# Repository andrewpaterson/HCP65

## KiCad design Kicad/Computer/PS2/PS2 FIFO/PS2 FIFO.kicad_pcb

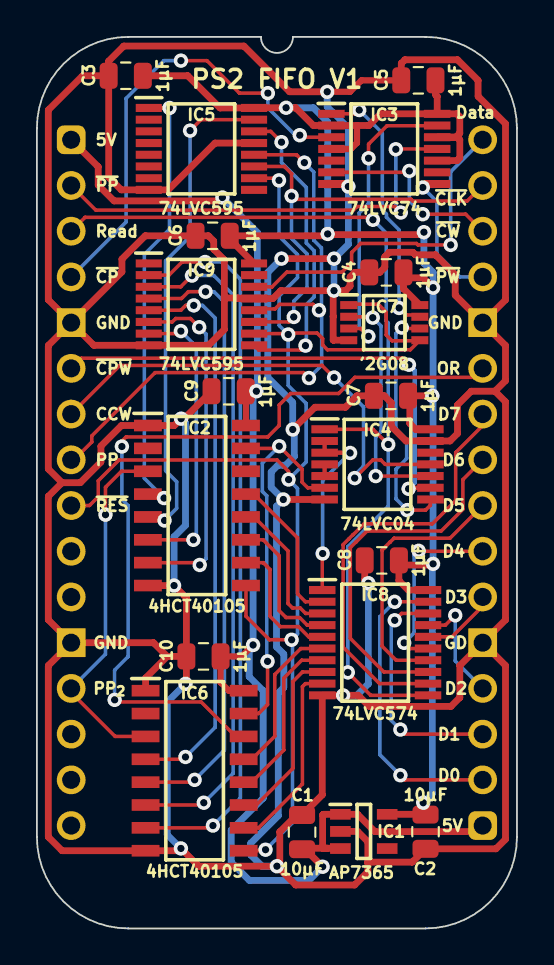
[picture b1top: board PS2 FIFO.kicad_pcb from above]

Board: 2 copper layers, 26.7 x 49.5 mm, 20 parts (0 on the bottom side), 48 nets.

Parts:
C1, C2: 10μF; C_0805
C3, C4, C5, C6, C7, C8, C9, C10: 1μF; C_0805
IC1: AP7365-33WG-7; SOT95P285X130-5N
IC2, IC6: CD74HCT40105M; SOIC127P600X175-16N
IC3: 74LVC74APW,118; SOP65P640X110-14N
IC4: 74LVC04APW,118; SOP65P640X110-14N
IC5, IC9: 74LVC595APW; SOP65P640X110-16N
IC7: 74LVC2G08DP-Q100H; SOP65P400X110-8N
IC8: 74LVC574APW,118; SOP65P640X110-20N
J1: Board 2x16 W22.86mm; DIP-32_Board_W22.86mm

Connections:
5V: C1.1, C9.1, C10.1, IC1.1 (6VIn), IC1.3 (EN), IC2.16 (5V), IC6.16 (5V), J1.1, J1.17
/3.3V: C2.1, C3.1, C4.1, C5.1, C6.1, C7.1, C8.1, IC1.5 (3.3VOut), IC3.2 (1D), IC3.4 (~1SD), IC3.10 (~2SD), IC3.12 (2D), IC3.14 (3V), IC4.14 (3V), IC5.16 (3V), IC7.8 (3V), IC8.20 (3V), IC9.16 (3V)
/Q0: IC2.4 (D0), IC5.1 (Q1)
/Q1: IC2.5 (D1), IC5.15 (Q0)
/Q2: IC2.6 (D2), IC9.7 (Q7)
/Q3: IC2.7 (D3), IC9.6 (Q6)
/Q4: IC6.4 (D0), IC9.5 (Q5)
/Q5: IC6.5 (D1), IC9.4 (Q4)
/Q6: IC6.6 (D2), IC9.3 (Q3)
/Q7: IC6.7 (D3), IC9.2 (Q2)
/Read_{2}: IC4.4 (2Y), IC4.5 (3A)
/S0: IC2.13 (Q0), IC8.2 (D0)
/S1: IC2.12 (Q1), IC8.3 (D1)
/S2: IC2.11 (Q2), IC8.4 (D2)
/S3: IC2.10 (Q3), IC8.5 (D3)
/S4: IC6.13 (Q0), IC8.6 (D4)
/S5: IC6.12 (Q1), IC8.7 (D5)
/S6: IC6.11 (Q2), IC8.8 (D6)
/S7: IC6.10 (Q3), IC8.9 (D7)
/~Clear Code Waiting: IC4.10 (5Y), IC7.2 (1B)
/~Clear Packet Waiting: IC4.8 (4Y), IC7.6 (2B)
/~Read: IC4.2 (1Y), IC4.3 (2A), IC8.1 (~OE)
/~Read_{3}: IC2.15 (~SO), IC4.6 (3Y), IC6.15 (~SO)
Clear Code Waiting: IC4.11 (5A), J1.7
Clear Packet Waiting: IC4.9 (4A), J1.6
D0: IC8.19 (Q0), J1.18
D1: IC8.18 (Q1), J1.19
D2: IC8.17 (Q2), J1.20
D3: IC8.16 (Q3), J1.22
D4: IC8.15 (Q4), J1.23
D5: IC8.14 (Q5), J1.24
D6: IC8.13 (Q6), J1.25
D7: IC8.12 (Q7), J1.26
Data: IC9.14 (DS), J1.32
GND: C1.2, C2.2, C3.2, C4.2, C5.2, C6.2, C7.2, C8.2, C9.2, C10.2, IC1.2 (GND), IC2.1 (~EN(TSC)), IC2.8 (GND), IC3.7 (GND), IC4.7 (GND), IC4.13 (6A), IC5.8 (GND), IC5.13 (~OE), IC6.1 (~EN(TSC)), IC6.8 (GND), IC7.4 (GND), IC8.10 (GND), IC9.8 (GND), IC9.13 (~OE), J1.5, J1.12, J1.21, J1.28
unnamed: IC3.1 (~1RD), IC7.7 (1Y)
unnamed: IC3.13 (~2RD), IC7.3 (2Y)
unnamed: IC5.14 (DS), IC9.9 (Q7S)
Output Ready: IC6.14 (DOR), J1.27
Packet Pulse: IC5.12 (STCP), IC9.12 (STCP), J1.8
Packet Pulse_{2}: IC2.3 (SI), IC6.3 (SI), J1.13
Read: IC4.1 (1A), IC8.11 (CP), J1.3
~Clock: IC5.11 (SHCP), IC9.11 (SHCP), J1.31
~Code Pulse: IC3.3 (1CP), J1.4
~Code Waiting: IC3.6 (~1Q), J1.30
~Packet Pulse: IC3.11 (2CP), J1.2
~Packet Waiting: IC3.8 (~2Q), J1.29
~Reset: IC2.9 (MR), IC5.10 (~MR), IC6.9 (MR), IC7.1 (1A), IC7.5 (2A), IC9.10 (~MR), J1.9

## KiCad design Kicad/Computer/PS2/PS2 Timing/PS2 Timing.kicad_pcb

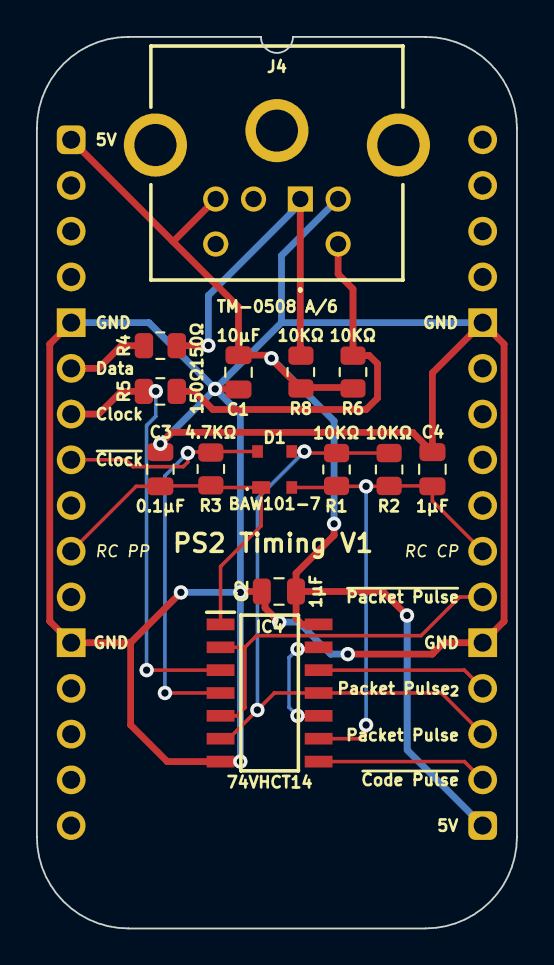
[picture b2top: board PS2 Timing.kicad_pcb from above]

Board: 2 copper layers, 26.7 x 49.5 mm, 15 parts (0 on the bottom side), 14 nets.

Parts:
C1: 10μF; C_0805
C2, C4: 1μF; C_0805
C3: 0.1μF; C_0805
D1: BAW101-7; BAW1017
IC4: 74VHCT14AM; SOIC127P600X175-14N
J2: Board 2x16 W22.86mm; DIP-32_Board_W22.86mm
J4: TM-0508 A/6; TM0508A6
R1, R2, R6, R8: 10KΩ; R_0805
R3: 4.7KΩ; R_0805
R4, R5: 150Ω; R_0805

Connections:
5V: C1.1, C2.1, IC4.14 (5V), J2.1, J2.17, J4.4, R6.2, R8.2
/Clock_{IN}: J4.5, R5.1, R6.1
/Data_{IN}: J4.1, R4.1, R8.1
/~Packet Pulse_{2}: IC4.10 (5Y), IC4.13 (6A)
Clock: IC4.3 (2A), J2.7, R5.2
Data: J2.6, R4.2
GND: C1.2, C2.2, C3.2, C4.2, IC4.7 (GND), J2.5, J2.12, J2.21, J2.28, J4.3
Packet Pulse: D1.3 (A2), IC4.6 (3Y), IC4.11 (5A), J2.19, R1.1, R2.1
Packet Pulse_{2}: IC4.12 (6Y), J2.20
RC Code Pulse: C4.1, D1.2 (K2), IC4.9 (4A), J2.23, R1.2, R2.2
RC Packet Pulse: C3.1, D1.1 (K1), IC4.1 (1A), J2.10, R3.2
~Clock: D1.4 (A1), IC4.4 (2Y), J2.8, R3.1
~Code Pulse: IC4.8 (4Y), J2.18
~Packet Pulse: IC4.2 (1Y), IC4.5 (3A), J2.22

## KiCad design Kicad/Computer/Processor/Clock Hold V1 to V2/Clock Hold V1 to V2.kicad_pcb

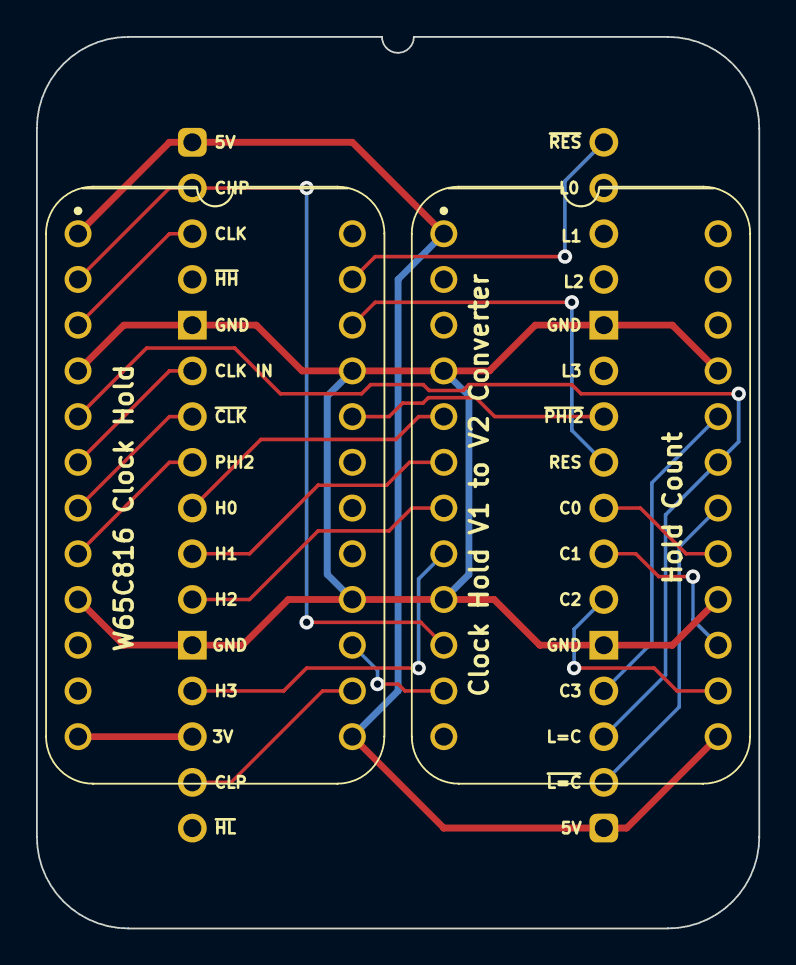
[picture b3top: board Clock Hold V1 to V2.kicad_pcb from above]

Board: 2 copper layers, 40.1 x 49.5 mm, 3 parts (0 on the bottom side), 23 nets.

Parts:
B22: W65C816 Clock Hold; HCP65_W65C816_Clock_Hold
B23: Hold Count; HCP65_Hold_Count
J1: Board 2x16 W22.86mm; DIP-32_Board_W22.86mm_Nak

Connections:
3.3V: B22.12 (~Hold_Low), J1.14
5V: B22.1 (5V), B22.13 (5V), B23.1 (5V), B23.13 (5V), J1.1, J1.17
/~CHP: B22.15 (~CLK_High_Pulse), B23.11 (~CLK_High_Pulse)
C0: B23.17 (Count0), J1.24
C1: B23.15 (Count1), J1.23
C2: B23.14 (Count2), J1.22
C3: B23.20 (Count3), J1.20
CHP: B22.2 (CLK_High_Pulse), B23.10 (CLK_High_Pulse), J1.2
CLK: B22.3 (CLK), J1.3
CLK IN: B22.6 (CLK_IN), J1.6
CLP: B22.14 (CLK_Low_Pulse), J1.15
GND: B22.4 (GND), B22.9 (GND), B22.16 (GND), B22.21 (GND), B23.4 (GND), B23.9 (GND), B23.16 (GND), B23.21 (GND), J1.5, J1.12, J1.21, J1.28
H0: B23.5 (Hold0), J1.9
H1: B23.6 (Hold1), J1.10
H2: B23.7 (Hold2), J1.11
H3: B23.8 (Hold3), J1.13
L=C: B22.5 (~Hold_High), B23.19 (L=C), J1.19
PHI2: B22.8 (PHI2), J1.8
Reset: B22.22 (Reset), J1.25
~CLK: B22.7 (~CLK), J1.7
~L=C: B23.18 (~L=C), J1.18
~PHI2: B22.20 (~PHI2), J1.26
~Reset: B22.23 (~Reset), J1.32

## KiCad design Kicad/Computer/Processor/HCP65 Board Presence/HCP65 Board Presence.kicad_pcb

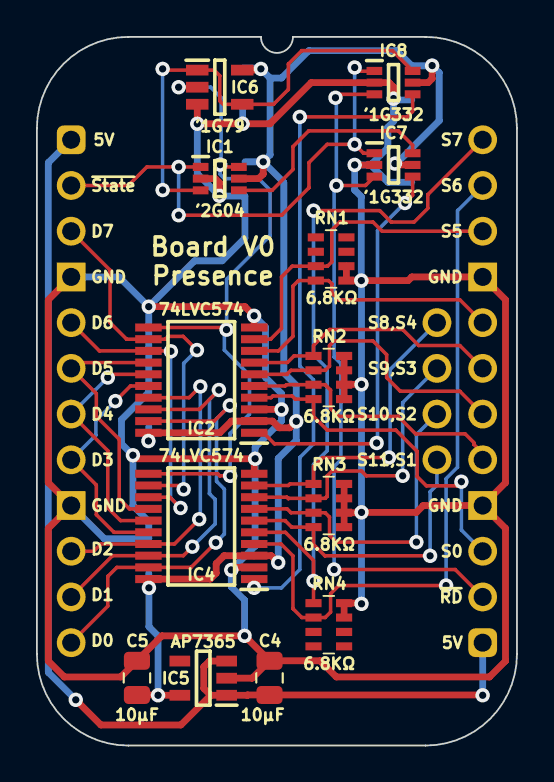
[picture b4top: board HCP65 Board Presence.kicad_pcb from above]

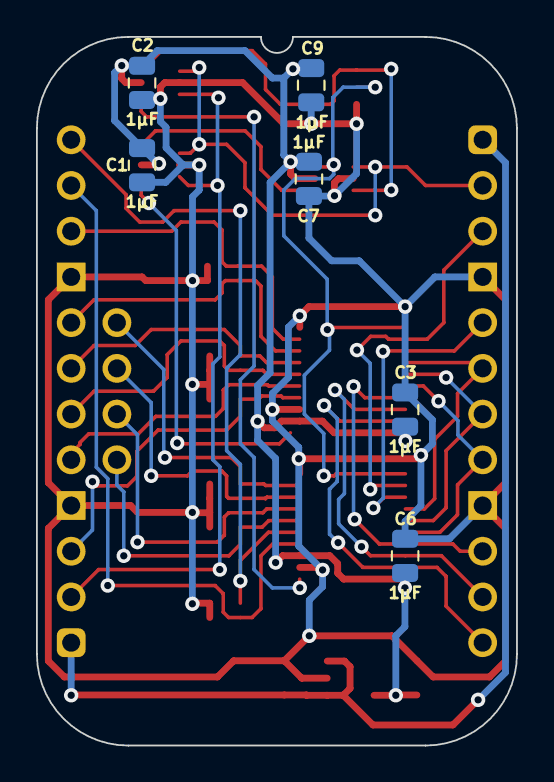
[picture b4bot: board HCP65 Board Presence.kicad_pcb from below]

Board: 2 copper layers, 26.7 x 39.4 mm, 21 parts (7 on the bottom side), 30 nets.

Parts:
C1, C2, C3, C6, C7, C9: 1μF; C_0805
C4, C5: 10µF; C_0805
IC1: 74LVC2G04GW-Q100H; SOP65P210X110-6N
IC2, IC4: 74LVC574APW,118; SOP65P640X110-20N
IC5: AP7365-33WG-7; SOT95P285X130-5N
IC6: 74LVC1G79GV,125; SOT95P275X110-5N
IC7, IC8: 74LVC1G332GW-Q100H; SOP65P210X110-6N
J1: Board 2x12 W22.86mm; DIP-24_Board_W22.86mm
J3: Conn_01x04_Pin; PinHeader_1x04_P2.54mm_Vertical
RN1, RN2, RN3, RN4: CAY16-682J4LF; CAY16-J4

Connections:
5V: C4.1, IC5.1 (6VIn), IC5.3 (EN), J1.1, J1.13
/3.3V: C1.1, C2.1, C3.1, C5.1, C6.1, C7.1, C9.1, IC1.5 (3V), IC2.2 (D0), IC2.20 (3V), IC4.3 (D1), IC4.20 (3V), IC5.5 (3.3VOut), IC6.5 (3V), IC7.5 (3V), IC8.5 (3V)
/Q: IC1.3 (2A), IC6.1 (D), IC6.4 (Q), IC8.6 (C)
/State: IC1.6 (1Y), IC2.11 (CP), IC4.11 (CP), IC6.2 (CP)
/~Q: IC1.4 (2Y), IC7.6 (C)
/~Read State0: IC2.1 (~OE), IC7.4 (Y)
/~Read State1: IC4.1 (~OE), IC8.4 (Y)
D0: IC2.19 (Q0), IC4.19 (Q0), J1.12
D1: IC2.18 (Q1), IC4.18 (Q1), J1.11
D2: IC2.17 (Q2), IC4.17 (Q2), J1.10
D3: IC2.16 (Q3), IC4.16 (Q3), J1.8
D4: IC2.15 (Q4), IC4.15 (Q4), J1.7
D5: IC2.14 (Q5), IC4.14 (Q5), J1.6
D6: IC2.13 (Q6), IC4.13 (Q6), J1.5
D7: IC2.12 (Q7), IC4.12 (Q7), J1.3
GND: C1.2, C2.2, C3.2, C4.2, C5.2, C6.2, C7.2, C9.2, IC1.2 (GND), IC2.3 (D1), IC2.10 (GND), IC4.2 (D0), IC4.10 (GND), IC5.2 (GND), IC6.3 (GND), IC7.2 (GND), IC8.2 (GND), J1.4, J1.9, J1.16, J1.21, RN1.5 (R4), RN1.6 (R3), RN2.5 (R4), RN2.6 (R3), RN2.7 (R2), RN2.8 (R1), RN3.5 (R4), RN3.6 (R3), RN3.7 (R2), RN3.8 (R1), RN4.7 (R2), RN4.8 (R1)
S0: IC2.4 (D2), J1.15, RN2.4 (R4)
S1: IC2.5 (D3), J1.17, RN2.3 (R3)
S2: IC2.6 (D4), J1.18, RN2.2 (R2)
S3: IC2.7 (D5), J1.19, RN2.1 (R1)
S4: IC2.8 (D6), J1.20, RN1.4 (R4)
S5: IC2.9 (D7), J1.22, RN1.3 (R3)
S6: IC4.4 (D2), J1.23, RN4.2 (R2)
S7: IC4.5 (D3), J1.24, RN4.1 (R1)
S8: IC4.6 (D4), J3.4, RN3.4 (R4)
S9: IC4.7 (D5), J3.3, RN3.3 (R3)
S10: IC4.8 (D6), J3.2, RN3.2 (R2)
S11: IC4.9 (D7), J3.1, RN3.1 (R1)
~RD: IC7.3 (B), IC8.3 (B), J1.14
~State: IC1.1 (1A), IC7.1 (A), IC8.1 (A), J1.2

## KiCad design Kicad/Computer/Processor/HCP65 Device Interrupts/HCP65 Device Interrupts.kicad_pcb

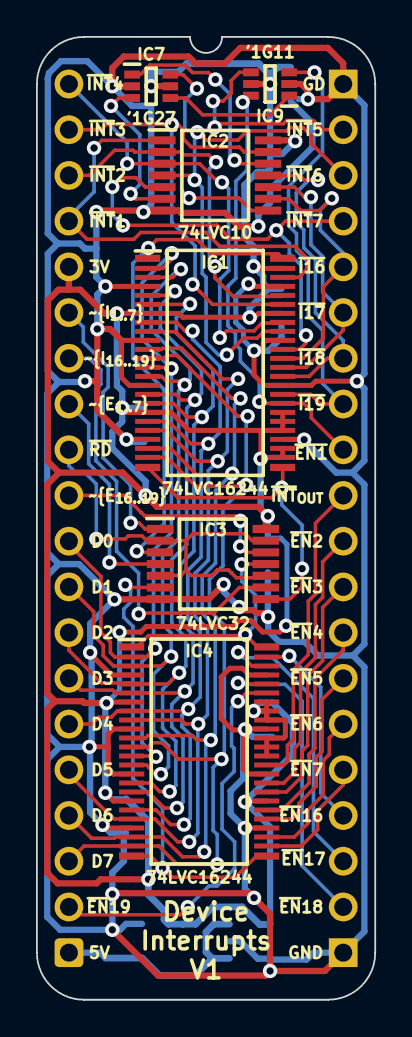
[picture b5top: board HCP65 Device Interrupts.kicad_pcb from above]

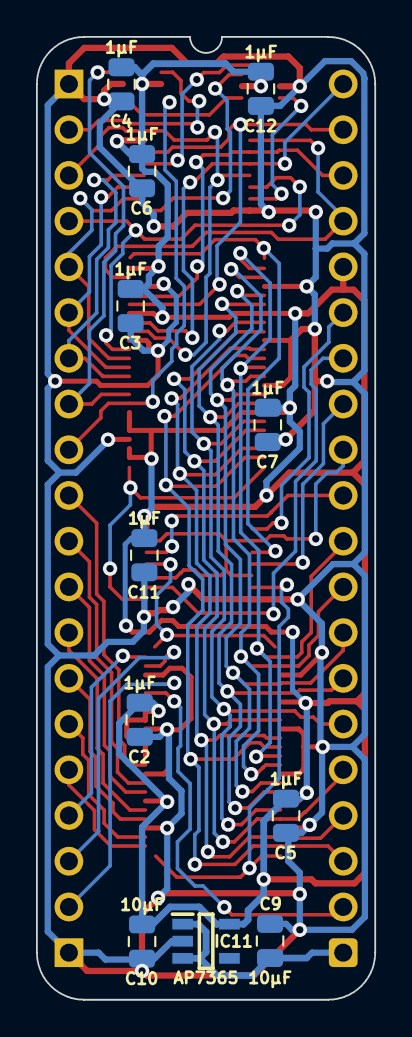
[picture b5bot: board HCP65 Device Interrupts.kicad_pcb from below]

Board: 2 copper layers, 18.8 x 53.5 mm, 18 parts (11 on the bottom side), 47 nets.

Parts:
C2, C3, C4, C5, C6, C7, C11, C12: 1μF; C_0805
C9, C10: 10μF; C_0805
IC1, IC4: 74LVC16244ADGG,112; 74LVC16244ADGG112
IC2: SN74LVC10APWR; SOP65P640X120-14N
IC3: 74LVC32APW,118; SOP65P640X110-14N
IC7: 74LVC1G27GW,125; SOP65P210X110-6N
IC9: 74LVC1G11GW-Q100H; SOP65P210X110-6N
IC11: AP7365-33WG-7; SOT95P285X130-5N
J2: Board 2x20 W15.24mm; DIP-40_Board_W15.24mm

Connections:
3.3V: C2.1, C3.1, C4.1, C5.1, C6.1, C7.1, C10.1, C11.1, C12.1, IC1.7 (3V), IC1.18 (3V), IC1.26 (4A3), IC1.27 (4A2), IC1.29 (4A1), IC1.30 (4A0), IC1.31 (3V), IC1.42 (3V), IC1.47 (1A0), IC2.14 (3V), IC3.14 (3V), IC4.7 (3V), IC4.18 (3V), IC4.31 (3V), IC4.36 (3A0), IC4.37 (2A3), IC4.38 (2A2), IC4.40 (2A1), IC4.41 (2A0), IC4.42 (3V), IC7.5 (3V), IC9.5 (3V), IC11.5 (3.3VOut), J2.5
5V: C9.1, IC11.1 (6VIn), IC11.3 (EN), J2.20
/~Read Device Enable_{ 1..7}: IC3.6 (2Y), IC4.24 (4~OE), IC4.25 (3~OE)
/~Read Device Enable_{ 16..19}: IC3.11 (4Y), IC4.1 (1~OE), IC4.48 (2~OE)
/~Read Device Interrupt_{ 1..7}: IC1.1 (1~OE), IC1.48 (2~OE), IC3.3 (1Y)
/~Read Device Interrupt_{ 16..19}: IC1.24 (4~OE), IC1.25 (3~OE), IC3.8 (3Y)
D0: IC1.2 (1Y0), IC1.13 (3Y0), IC4.2 (1Y0), IC4.13 (3Y0), J2.11
D1: IC1.3 (1Y1), IC1.14 (3Y1), IC4.3 (1Y1), IC4.14 (3Y1), J2.12
D2: IC1.5 (1Y2), IC1.16 (3Y2), IC4.5 (1Y2), IC4.16 (3Y2), J2.13
D3: IC1.6 (1Y3), IC1.17 (3Y3), IC4.6 (1Y3), IC4.17 (3Y3), J2.14
D4: IC1.8 (2Y0), IC1.19 (4Y0), IC4.8 (2Y0), IC4.19 (4Y0), J2.15
D5: IC1.9 (2Y1), IC1.20 (4Y1), IC4.9 (2Y1), IC4.20 (4Y1), J2.16
D6: IC1.11 (2Y2), IC1.22 (4Y2), IC4.11 (2Y2), IC4.22 (4Y2), J2.17
D7: IC1.12 (2Y3), IC1.23 (4Y3), IC4.12 (2Y3), IC4.23 (4Y3), J2.18
GND: C2.2, C3.2, C4.2, C5.2, C6.2, C7.2, C9.2, C10.2, C11.2, C12.2, IC1.4 (GND), IC1.10 (GND), IC1.15 (GND), IC1.21 (GND), IC1.28 (GND), IC1.34 (GND), IC1.39 (GND), IC1.45 (GND), IC2.7 (GND), IC3.7 (GND), IC4.4 (GND), IC4.10 (GND), IC4.15 (GND), IC4.21 (GND), IC4.28 (GND), IC4.34 (GND), IC4.39 (GND), IC4.45 (GND), IC7.2 (GND), IC9.2 (GND), IC11.2 (GND), J2.21, J2.40
unnamed: IC2.12 (1Y), IC7.1 (A)
unnamed: IC2.6 (2Y), IC7.3 (B)
unnamed: IC2.8 (3Y), IC7.6 (C)
unnamed: IC7.4 (Y), IC9.1 (A)
~Device Enable_{ 1..7}: IC3.4 (2A), J2.8
~Device Enable_{ 16..19}: IC3.12 (4A), J2.10
~Device Interrupt_{ 1..7}: IC3.1 (1A), J2.6
~Device Interrupt_{ 16..19}: IC3.9 (3A), J2.7
~Enable_{Device}1: IC4.35 (3A1), J2.31
~Enable_{Device}2: IC4.33 (3A2), J2.30
~Enable_{Device}3: IC4.32 (3A3), J2.29
~Enable_{Device}4: IC4.30 (4A0), J2.28
~Enable_{Device}5: IC4.29 (4A1), J2.27
~Enable_{Device}6: IC4.27 (4A2), J2.26
~Enable_{Device}7: IC4.26 (4A3), J2.25
~Enable_{Device}16: IC4.47 (1A0), J2.24
~Enable_{Device}17: IC4.46 (1A1), J2.23
~Enable_{Device}18: IC4.44 (1A2), J2.22
~Enable_{Device}19: IC4.43 (1A3), J2.19
~INT: IC9.4 (Y), J2.39
~Interrupt_{Device}1: IC1.46 (1A1), IC2.1 (1A), J2.4
~Interrupt_{Device}2: IC1.44 (1A2), IC2.2 (1B), J2.3
~Interrupt_{Device}3: IC1.43 (1A3), IC2.13 (1C), J2.2
~Interrupt_{Device}4: IC1.41 (2A0), IC2.3 (2A), J2.1
~Interrupt_{Device}5: IC1.40 (2A1), IC2.4 (2B), J2.38
~Interrupt_{Device}6: IC1.38 (2A2), IC2.5 (2C), J2.37
~Interrupt_{Device}7: IC1.37 (2A3), IC2.9 (3A), J2.36
~Interrupt_{Device}16: IC1.36 (3A0), IC2.10 (3B), J2.35
~Interrupt_{Device}17: IC1.35 (3A1), IC2.11 (3C), J2.34
~Interrupt_{Device}18: IC1.33 (3A2), IC9.3 (B), J2.33
~Interrupt_{Device}19: IC1.32 (3A3), IC9.6 (C), J2.32
~RD: IC3.2 (1B), IC3.5 (2B), IC3.10 (3B), IC3.13 (4B), J2.9

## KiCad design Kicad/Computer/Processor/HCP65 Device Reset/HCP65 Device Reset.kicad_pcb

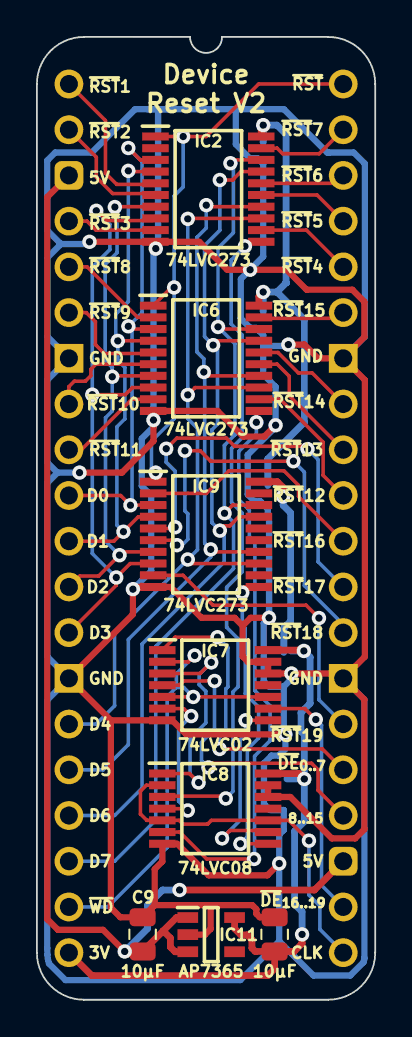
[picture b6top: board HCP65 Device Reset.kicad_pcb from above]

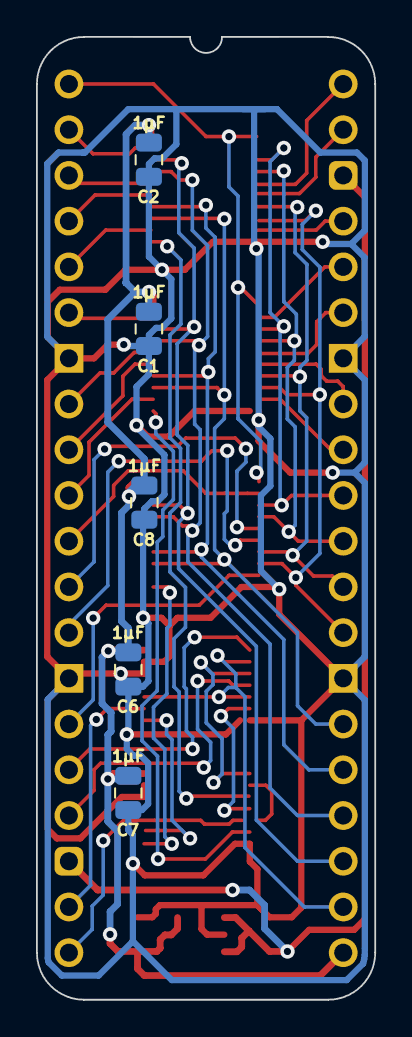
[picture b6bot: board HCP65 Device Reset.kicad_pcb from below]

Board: 2 copper layers, 18.8 x 53.5 mm, 14 parts (5 on the bottom side), 42 nets.

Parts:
C1, C2, C6, C7, C8: 1μF; C_0805
C9, C10: 10μF; C_0805
IC2, IC6, IC9: 74LVC273PW,118; SOP65P640X110-20N
IC7: 74LVC02APW,118; SOP65P640X110-14N
IC8: 74LVC08APW,112; SOP65P640X110-14N
IC11: AP7365-33WG-7; SOT95P285X130-5N
J4: Board 2x20 W15.24mm; DIP-40_Board_W15.24mm

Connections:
3.3V: C1.1, C2.1, C6.1, C7.1, C8.1, C10.1, IC2.20 (3V), IC6.20 (3V), IC7.14 (3V), IC8.14 (3V), IC9.20 (3V), IC11.5 (3.3VOut), J4.20
5V: C9.1, IC11.1 (6VIn), IC11.3 (EN), J4.3, J4.23
/Write Device Reset_{ 1..7}: IC7.3 (1Y), IC8.1 (1A)
/Write Device Reset_{ 1..7}·~CLK: IC2.11 (CP), IC8.3 (1Y)
/Write Device Reset_{ 8..15}: IC7.6 (2Y), IC8.4 (2A)
/Write Device Reset_{ 8..15}·~CLK: IC6.11 (CP), IC8.6 (2Y)
/Write Device Reset_{ 16..19}: IC7.8 (3Y), IC8.9 (3A)
/Write Device Reset_{ 16..19}·~CLK: IC8.8 (3Y), IC9.11 (CP)
D0: IC2.3 (D0), IC6.3 (D0), IC9.3 (D0), J4.10
D1: IC2.4 (D1), IC6.4 (D1), IC9.4 (D1), J4.11
D2: IC2.7 (D2), IC6.7 (D2), IC9.7 (D2), J4.12
D3: IC2.8 (D3), IC6.8 (D3), IC9.8 (D3), J4.13
D4: IC2.13 (D4), IC6.13 (D4), IC9.13 (D4), J4.15
D5: IC2.14 (D5), IC6.14 (D5), IC9.14 (D5), J4.16
D6: IC2.17 (D6), IC6.17 (D6), IC9.17 (D6), J4.17
D7: IC2.18 (D7), IC6.18 (D7), IC9.18 (D7), J4.18
GND: C1.2, C2.2, C6.2, C7.2, C8.2, C9.2, C10.2, IC2.10 (GND), IC6.10 (GND), IC7.7 (GND), IC7.12 (4A), IC7.13 (4B), IC8.7 (GND), IC8.12 (4A), IC8.13 (4B), IC9.10 (GND), IC11.2 (GND), J4.7, J4.14, J4.27, J4.34
~CLK: IC8.2 (1B), IC8.5 (2B), IC8.10 (3B), J4.21
~Device Reset_{ 1..7}: IC7.1 (1A), J4.25
~Device Reset_{ 8..15}: IC7.4 (2A), J4.24
~Device Reset_{ 16..19}: IC7.9 (3A), J4.22
~Reset: IC2.1 (~MR), IC6.1 (~MR), IC9.1 (~MR), J4.40
~Reset_{Device}1: IC2.5 (Q1), J4.1
~Reset_{Device}2: IC2.6 (Q2), J4.2
~Reset_{Device}3: IC2.9 (Q3), J4.4
~Reset_{Device}4: IC2.12 (Q4), J4.36
~Reset_{Device}5: IC2.15 (Q5), J4.37
~Reset_{Device}6: IC2.16 (Q6), J4.38
~Reset_{Device}7: IC2.19 (Q7), J4.39
~Reset_{Device}8: IC6.2 (Q0), J4.5
~Reset_{Device}9: IC6.5 (Q1), J4.6
~Reset_{Device}10: IC6.6 (Q2), J4.8
~Reset_{Device}11: IC6.9 (Q3), J4.9
~Reset_{Device}12: IC6.12 (Q4), J4.31
~Reset_{Device}13: IC6.15 (Q5), J4.32
~Reset_{Device}14: IC6.16 (Q6), J4.33
~Reset_{Device}15: IC6.19 (Q7), J4.35
~Reset_{Device}16: IC9.2 (Q0), J4.30
~Reset_{Device}17: IC9.5 (Q1), J4.29
~Reset_{Device}18: IC9.6 (Q2), J4.28
~Reset_{Device}19: IC9.9 (Q3), J4.26
~WD: IC7.2 (1B), IC7.5 (2B), IC7.10 (3B), J4.19

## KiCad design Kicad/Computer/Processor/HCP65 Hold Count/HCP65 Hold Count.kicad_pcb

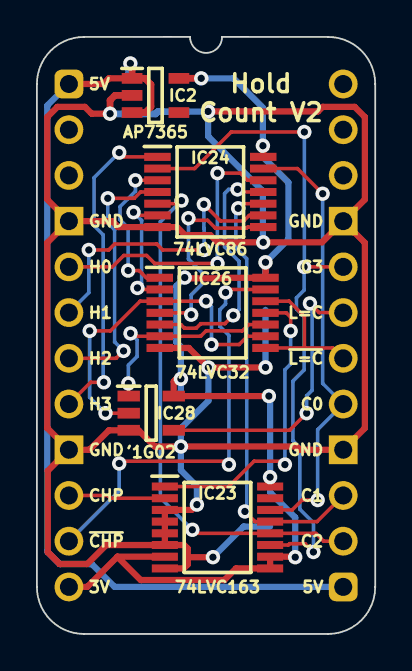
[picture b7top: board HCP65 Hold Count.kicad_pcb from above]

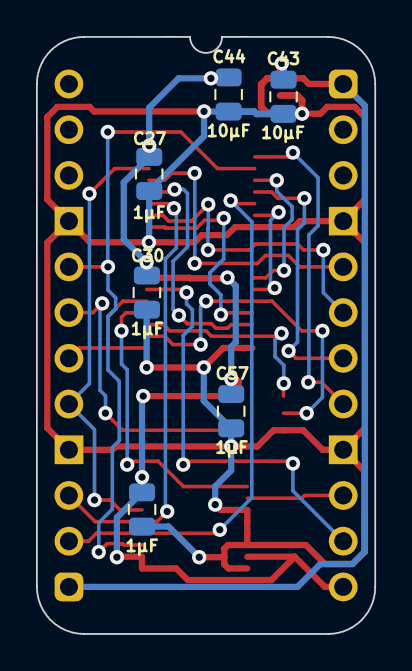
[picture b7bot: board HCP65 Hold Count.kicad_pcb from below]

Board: 2 copper layers, 18.8 x 33.2 mm, 12 parts (6 on the bottom side), 22 nets.

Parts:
C25, C27, C30, C57: 1μF; C_0805
C43, C44: 10μF; C_0805
IC2: AP7365-33WG-7; SOT95P285X130-5N
IC23: 74LVC163PW,118; SOP65P640X110-16N
IC24: SN74LVC86APWR; SOP65P640X120-14N
IC26: 74LVC32APW,118; SOP65P640X110-14N
IC28: 74LVC1G02GV,125; SOT95P275X110-5N
J1: Board 2x12 W15.24mm; DIP-24_Board_W15.24mm

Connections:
3.3V: C25.1, C27.1, C30.1, C44.1, C57.1, IC2.5 (3.3VOut), IC23.7 (CEP), IC23.9 (~PE), IC23.10 (CET), IC23.16 (3V), IC24.14 (3V), IC26.14 (3V), IC28.5 (3V), J1.12
5V: C43.1, IC2.1 (6VIn), IC2.3 (EN), J1.1, J1.13
/~L0=C0: IC24.11 (4Y), IC26.5 (2B)
/~L1=C1: IC24.8 (3Y), IC26.4 (2A)
/~L2=C2: IC24.6 (2Y), IC26.2 (1B)
/~L3=C3: IC24.3 (1Y), IC26.1 (1A)
/~L_{1+0=C_{1+0}}: IC26.6 (2Y), IC26.10 (3B), IC28.1 (B)
/~L_{3+2=C_{3+2}}: IC26.3 (1Y), IC26.9 (3A), IC28.2 (A)
/~Reset Counter: IC23.1 (~MR), IC26.11 (4Y)
CLK High Pulse: IC23.2 (CP), J1.10
Count0: IC23.14 (Q0), IC24.13 (4B), J1.17
Count1: IC23.13 (Q1), IC24.10 (3B), J1.15
Count2: IC23.12 (Q2), IC24.5 (2B), J1.14
Count3: IC23.11 (Q3), IC24.2 (1B), J1.20
GND: C25.2, C27.2, C30.2, C43.2, C44.2, C57.2, IC2.2 (GND), IC23.3 (D0), IC23.4 (D1), IC23.5 (D2), IC23.6 (D3), IC23.8 (GND), IC24.7 (GND), IC26.7 (GND), IC28.3 (GND), J1.4, J1.9, J1.16, J1.21
L=C: IC28.4 (Y), J1.19
Latch0: IC24.12 (4A), J1.5
Latch1: IC24.9 (3A), J1.6
Latch2: IC24.4 (2A), J1.7
Latch3: IC24.1 (1A), J1.8
~CLK High Pulse: IC26.13 (4B), J1.11
~L=C: IC26.8 (3Y), IC26.12 (4A), J1.18
